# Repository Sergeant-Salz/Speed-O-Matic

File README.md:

# Speed'o'Matic

A small hardware/software project to build a velocity sensor for my [potato cannon](https://en.wikipedia.org/wiki/Potato_cannon).  
Using two strips of tinfoil stretched across a pipe, which are torn by the passing projectile, this system measures the travel time and calculates the velocity of the potato. Results are shown on a set of ultra-bright 7-segment displays.

## Overview

The goal of this project is to measure the velocity of a potato accelerated inside a PVC tube. The design uses a simple two-barrier timing system where the time difference between two breakpoints is used to estimate the projectile's average velocity.

To make the system detachable and reliable, a separate piece of pipe (matching the barrel diameter) is used. Two thin strips of aluminum foil are stretched across this pipe at fixed distances—these act as breakable electrical contacts. When the projectile passes through, it breaks the foils, triggering the timing logic.

The circuit is built around an ATMega microcontroller that measures and displays the travel time and optionally computes the velocity. The following sections describe the circuit and software in more detail.

## Hardware

The ATMega microcontroller handles all logic and is powered via a simple linear regulator. With the currently used LM1084 regulator, the input voltage can range from 5V to 29V.

In addition to measuring time, the microcontroller also drives four 7-segment displays to show timing and status information. To ensure maximum brightness (important for outdoor use), the displays are not multiplexed. Each display is driven by its own MOS4511 driver IC. Combined with 91Ω segment resistors, this setup results in an extremely bright, easily readable output - even in direct sunlight.

An extra push-button is included for to reset the software after a completed measurment.

The schematic above shows the complete circuit design.

Below is an image of the assembled PCB.  
The unpopulated capacitor footprints in the foreground were included for optional input debouncing, in case the mechanical barrier setup introduced signal glitches. In practice, these capacitors were not necessary, but the footprints remain available for future use.

Also note the empty space in the top-left corner, which was intended for a USB-A receptacle. See the [To-Do / Known Issues](#to-do--known-issues) section for more information.

## Software

The microcontroller is programmed via the Arduino platform and [MiniCore](https://github.com/MCUdude/MiniCore) board support package. The core logic is implemented as a state machine in `lichtschranke.ino`, with board-specific port definitions in separate header files.

### State Descriptions

- **`INIT`**
  - Entered on boot or when the reset button is pressed.
  - Displays the status of the two barriers (0/1) to indicate whether they are intact.
  - Transitions to `CAPTURE` once both barriers remain intact for 1 second.

- **`CAPTURE`**
  - Waits for the first foil to break (first interrupt).
  - Displays all zeros.
  - Transitions to `TRIGGERED_0` if the first barrier is broken.

- **`TRIGGERED_0`**
  - Waits for the second foil to break.
  - Displays the elapsed time since the first barrier was broken.
  - Transitions to `CAPTURE_DONE` once the second barrier is triggered.

- **`CAPTURE_DONE`**
  - Indicates successful capture; both barriers have been broken in the correct order.
  - Displays the time delta in milliseconds.
  - Returns to `INIT` when the reset button is pressed.

- **`GENERAL_ERROR`**
  - Currently unused; reserved for future error handling scenarios.

```mermaid
graph TD;
    INIT-->CAPTURE;
    CAPTURE-->TRIGGERED_0;
    TRIGGERED_0-->CAPTURE_DONE;
```

## Calibration

### Setup Description

For calibration, I used a Siglent SDG1032X function generator to produce precise reference timings on the circuit’s interrupt pins. Waveforms were verified using a Rigol DS1054Z oscilloscope and found to be accurate within a few nanoseconds.

### Measurements

In nanosecond mode, the system was found to be accurate to within ±2%. The shortest measurable delay is around 16 ns, though for intervals below 100 ns, accuracy decreases due to timer resolution limits.

## To-Do / Known Issues

### Interrupt Pins

The barrier sensors are currently routed to general-purpose pins, requiring the use of pin-change interrupts instead of dedicated external interrupts. While functional, this requires additional code to determine which pin triggered the interrupt and its edge direction. Future versions should re-route these signals to the ATMega's external interrupt pins for cleaner and more efficient interrupt service routines.

### USB-A Connector

The board currently includes a footprint for a USB-A connector, originally intended as an alternate power source. However, USB-A is poorly suited for this purpose. Consider replacing it with a USB micro-B or USB-C connector, or removing it altogether in future revisions.

### LED Brightness

The displays may actually be *too* bright for some conditions. In future revisions, consider using higher-value segment resistors to reduce brightness and power consumption, especially for indoor or low-light use.

### Timing Accuracy

To achieve higher precision—especially in the low nanosecond range—it may be worthwhile to forgo the Arduino framework and implement the timing-critical functions in bare-metal C. This would provide greater control over the microcontroller's behavior and open the door to low-level optimizations that improve accuracy and determinism.

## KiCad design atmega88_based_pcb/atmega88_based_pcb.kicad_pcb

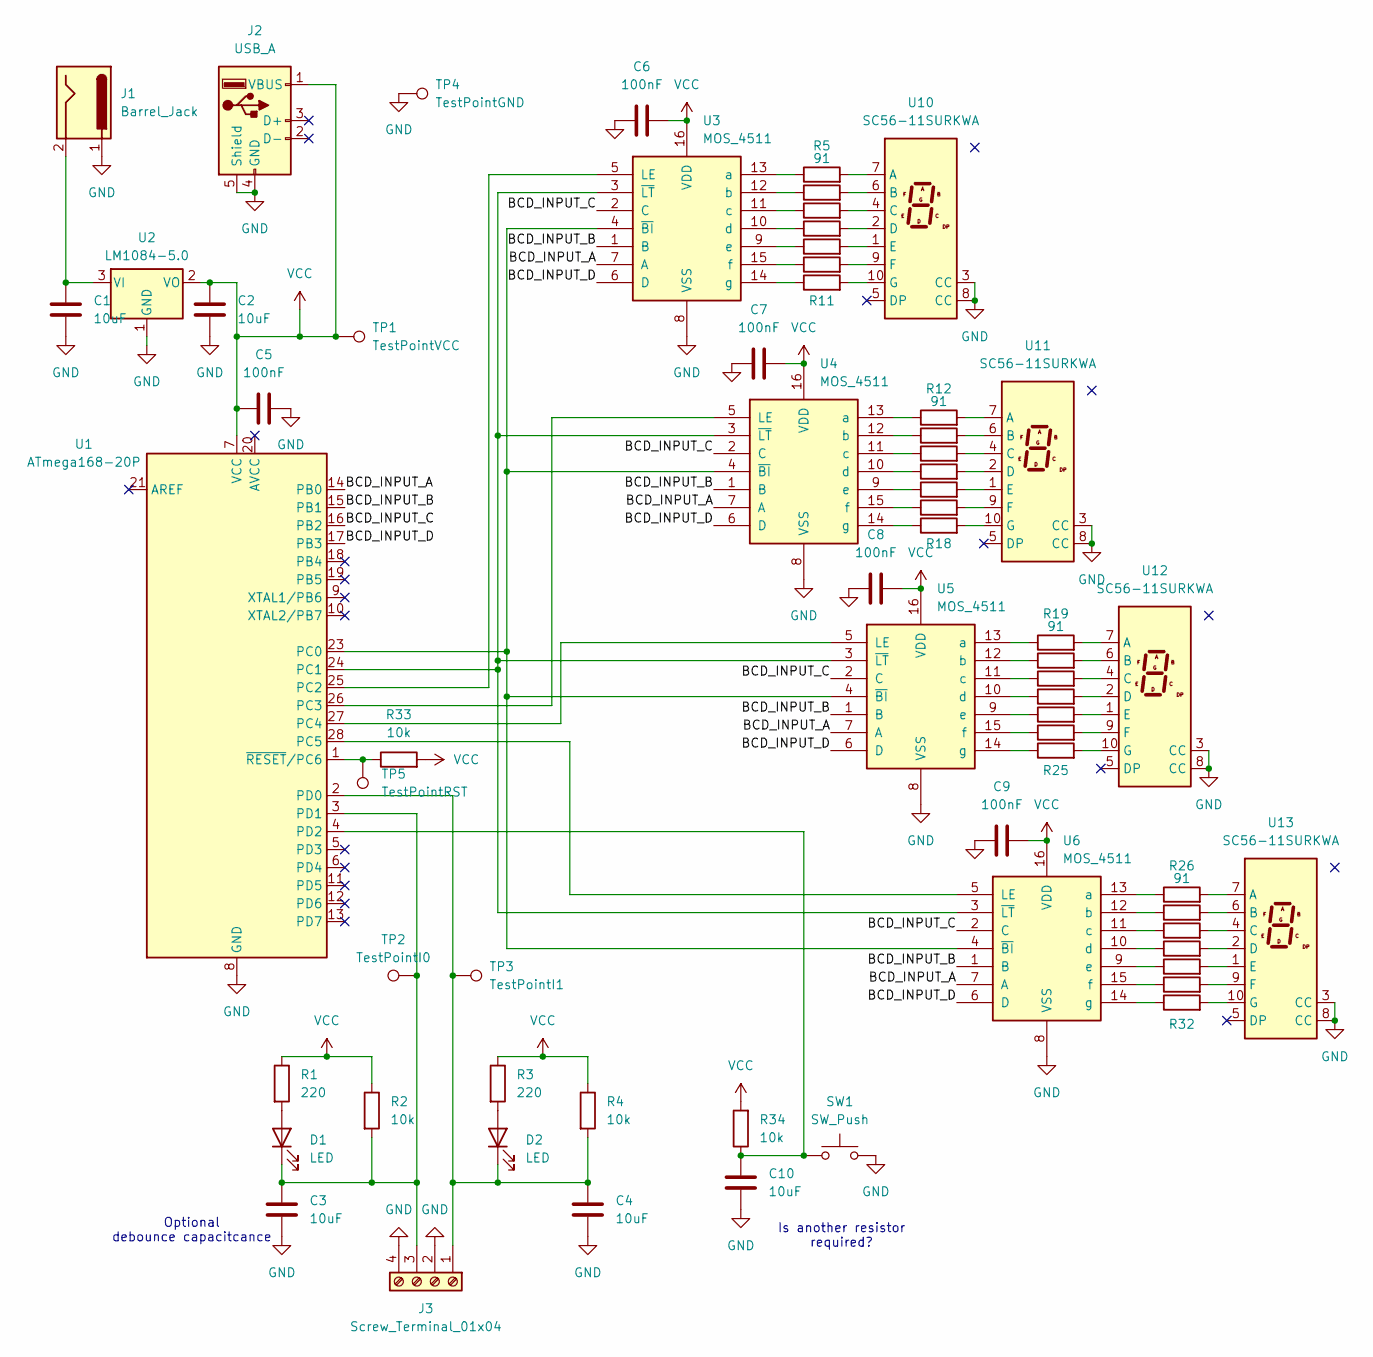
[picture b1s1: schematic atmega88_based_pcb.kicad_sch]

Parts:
C1, C2, C3, C4, C10: 10uF; CP_Radial_D10.0mm_P5.00mm
C5, C6, C7, C8, C9: 100nF; C_Axial_L3.8mm_D2.6mm_P7.50mm_Horizontal
D1, D2: LED; LED_D5.0mm
J1: Barrel_Jack; BarrelJack_CLIFF_FC68148S_SMT_Horizontal
J2: USB_A; USB_A_ASSMAN_AW
J3: Screw_Terminal_01x04; TerminalBlock_Phoenix_MPT-0,5-4-2.54_1x04_P2.54mm_Horizontal
R1, R3: 220; R_Axial_DIN0207_L6.3mm_D2.5mm_P7.62mm_Horizontal
R2, R4, R33, R34: 10k; R_Axial_DIN0207_L6.3mm_D2.5mm_P7.62mm_Horizontal
R5, R6, R7, R8, R9, R10, R11, R12, R13, R14, R15, R16, R17, R18, R19, R20, R21, R22, R23, R24, R25, R26, R27, R28, R29, R30, R31, R32: 91; R_Axial_DIN0207_L6.3mm_D2.5mm_P7.62mm_Horizontal
SW1: SW_Push; SW_SPST_Omron_B3F-40xx
TP1: TestPointVCC; TestPoint_Pad_1.0x1.0mm
TP2: TestPointI0; TestPoint_Pad_1.0x1.0mm
TP3: TestPointI1; TestPoint_Pad_1.0x1.0mm
TP4: TestPointGND; TestPoint_Pad_1.0x1.0mm
TP5: TestPointRST; TestPoint_Pad_1.0x1.0mm
U1: ATmega168-20P; DIP-28_W7.62mm
U2: LM1084-5.0; TO-220-3_Vertical
U3, U4, U5, U6: MOS_4511; DIP-16_W7.62mm
U10, U11, U12, U13: SC56-11SURKWA; D1X8K

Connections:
/BCD_INPUT_A: U1.14 (PB0), U3.7 (A), U4.7 (A), U5.7 (A), U6.7 (A)
/BCD_INPUT_B: U1.15 (PB1), U3.1 (B), U4.1 (B), U5.1 (B), U6.1 (B)
/BCD_INPUT_C: U1.16 (PB2), U3.2 (C), U4.2 (C), U5.2 (C), U6.2 (C)
/BCD_INPUT_D: U1.17 (PB3), U3.6 (D), U4.6 (D), U5.6 (D), U6.6 (D)
GND: C1.1, C2.1, C3.1, C4.1, C5.1, C6.2, C7.2, C8.2, C9.2, C10.1, J1.1, J2.4 (GND), J2.5 (Shield), J3.2, J3.4, SW1.2, TP4.1, U1.8 (GND), U1.22 (GND), U2.1 (GND), U3.8 (VSS), U4.8 (VSS), U5.8 (VSS), U6.8 (VSS), U10.3 (CC), U10.8 (CC), U11.3 (CC), U11.8 (CC), U12.3 (CC), U12.8 (CC), U13.3 (CC), U13.8 (CC)
unnamed: D1.2 (A), R1.2
unnamed: C3.2, D1.1 (K), J3.3, R2.2, TP2.1, U1.3 (PD1)
unnamed: D2.2 (A), R3.2
unnamed: C4.2, D2.1 (K), J3.1, R4.2, TP3.1, U1.2 (PD0)
unnamed: U1.23 (PC0), U3.4 (~BI), U4.4 (~BI), U5.4 (~BI), U6.4 (~BI)
unnamed: U1.24 (PC1), U3.3 (~LT), U4.3 (~LT), U5.3 (~LT), U6.3 (~LT)
unnamed: U1.25 (PC2), U3.5 (LE)
unnamed: U1.26 (PC3), U4.5 (LE)
unnamed: U1.27 (PC4), U5.5 (LE)
unnamed: U1.28 (PC5), U6.5 (LE)
unnamed: C10.2, R34.1, SW1.1, U1.4 (PD2)
unnamed: R33.1, TP5.1, U1.1 (~RESET/PC6)
unnamed: C1.2, J1.2, U2.3 (VI)
unnamed: R5.1, U3.13 (a)
unnamed: R6.1, U3.12 (b)
unnamed: R7.1, U3.11 (c)
unnamed: R8.1, U3.10 (d)
unnamed: R9.1, U3.9 (e)
unnamed: R10.1, U3.15 (f)
unnamed: R11.1, U3.14 (g)
unnamed: R12.1, U4.13 (a)
unnamed: R13.1, U4.12 (b)
unnamed: R14.1, U4.11 (c)
unnamed: R15.1, U4.10 (d)
unnamed: R16.1, U4.9 (e)
unnamed: R17.1, U4.15 (f)
unnamed: R18.1, U4.14 (g)
unnamed: R19.1, U5.13 (a)
unnamed: R20.1, U5.12 (b)
unnamed: R21.1, U5.11 (c)
unnamed: R22.1, U5.10 (d)
unnamed: R23.1, U5.9 (e)
unnamed: R24.1, U5.15 (f)
unnamed: R25.1, U5.14 (g)
unnamed: R26.1, U6.13 (a)
unnamed: R27.1, U6.12 (b)
unnamed: R28.1, U6.11 (c)
unnamed: R29.1, U6.10 (d)
unnamed: R30.1, U6.9 (e)
unnamed: R31.1, U6.15 (f)
unnamed: R32.1, U6.14 (g)
unnamed: R5.2, U10.7 (A)
unnamed: R6.2, U10.6 (B)
unnamed: R7.2, U10.4 (C)
unnamed: R8.2, U10.2 (D)
unnamed: R9.2, U10.1 (E)
unnamed: R10.2, U10.9 (F)
unnamed: R11.2, U10.10 (G)
unnamed: R12.2, U11.7 (A)
unnamed: R13.2, U11.6 (B)
unnamed: R14.2, U11.4 (C)
unnamed: R15.2, U11.2 (D)
unnamed: R16.2, U11.1 (E)
unnamed: R17.2, U11.9 (F)
unnamed: R18.2, U11.10 (G)
unnamed: R19.2, U12.7 (A)
unnamed: R20.2, U12.6 (B)
unnamed: R21.2, U12.4 (C)
unnamed: R22.2, U12.2 (D)
unnamed: R23.2, U12.1 (E)
unnamed: R24.2, U12.9 (F)
unnamed: R25.2, U12.10 (G)
unnamed: R26.2, U13.7 (A)
unnamed: R27.2, U13.6 (B)
unnamed: R28.2, U13.4 (C)
unnamed: R29.2, U13.2 (D)
unnamed: R30.2, U13.1 (E)
unnamed: R31.2, U13.9 (F)
unnamed: R32.2, U13.10 (G)
VCC: C2.2, C5.2, C6.1, C7.1, C8.1, C9.1, J2.1 (VBUS), R1.1, R2.1, R3.1, R4.1, R33.2, R34.2, TP1.1, U1.7 (VCC), U2.2 (VO), U3.16 (VDD), U4.16 (VDD), U5.16 (VDD), U6.16 (VDD)

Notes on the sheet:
Optional debounce capacitcance
Is another resistor required?

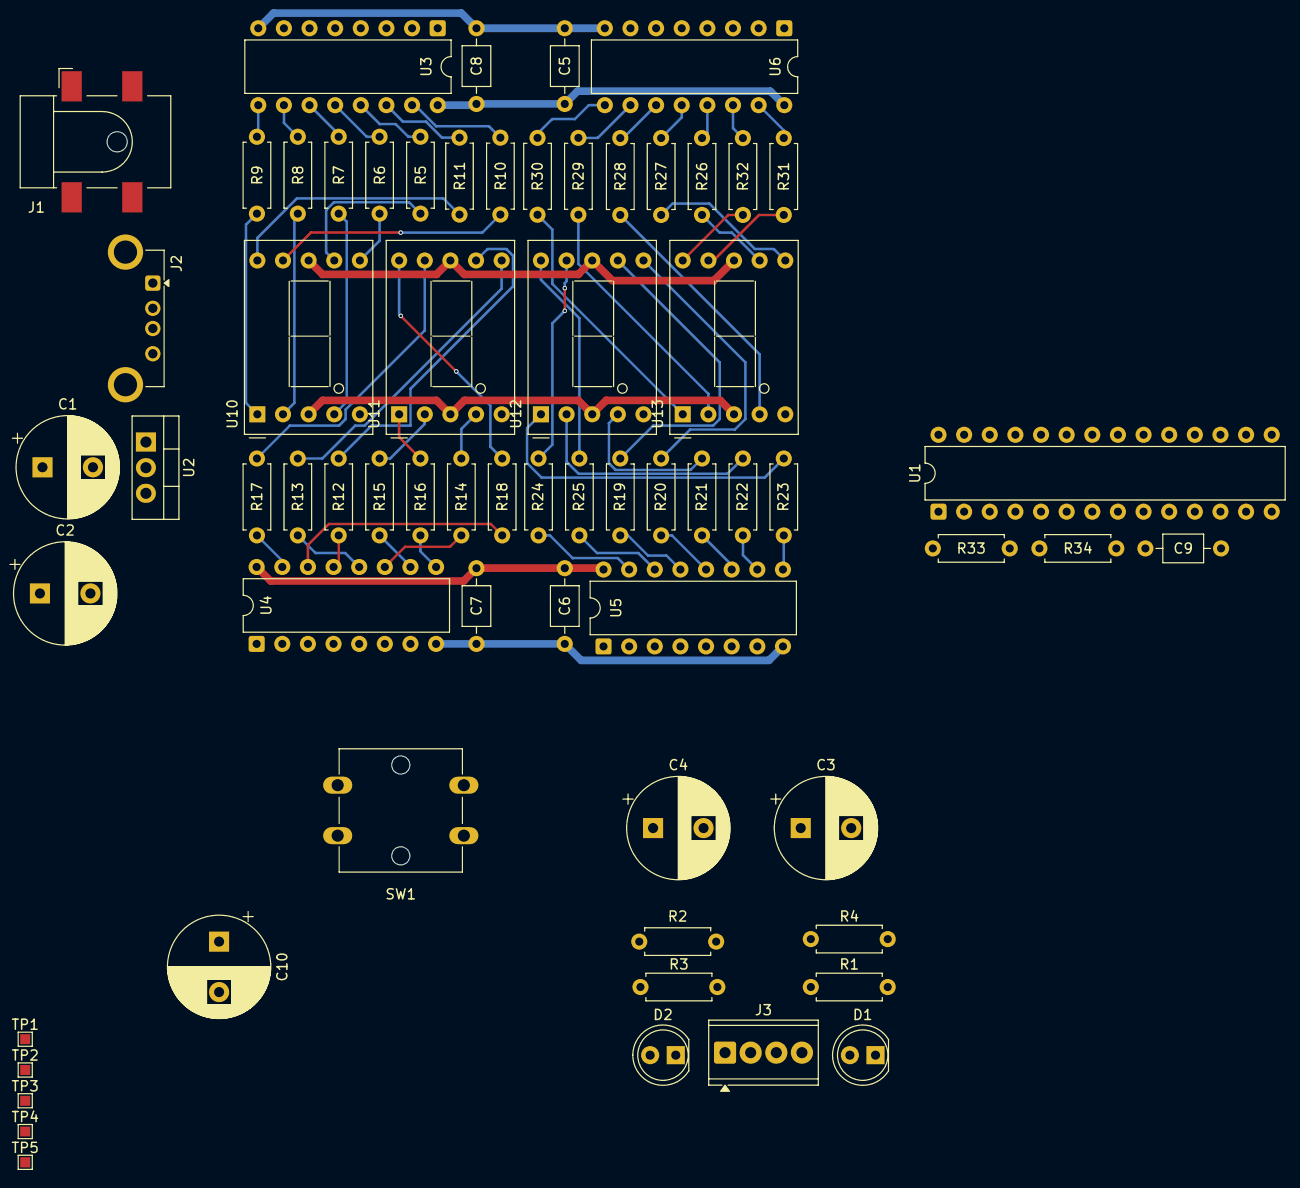
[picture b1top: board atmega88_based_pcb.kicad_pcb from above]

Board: 2 copper layers, 65 parts (0 on the bottom side), 75 nets.

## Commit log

2025-03-23 Initial arduino src code commit
2025-03-23 Fixed INIT transition, interrupt pins and logging improvement
2025-03-24 Fix latching for display drivers Fix time delta computation
2025-03-24 Initial commit of KiCad files
2025-04-15 Small fixes to comments and debug macro
2025-04-15 Added ATmega168 board pin definitions
2025-04-15 Tied AVCC to VCC and changed interrupt pins to use PD3/4 for external interrupts instead of PCINT
2025-04-23 Added README
2025-04-23 Fix mermaid diagram
2025-04-23 PCINT first draft
2025-04-24 Added some page metadata to schematic
2025-04-24 Added schematic to README
2025-04-24 Changed title
2025-04-24 Renamed src code directory^
2025-04-24 Added more general attach/detachInterrupt overwrites
2025-04-24 Added reset button support
2025-04-24 Fixed number display order
2025-04-24 Changed interrupt order to match user intuition
2025-04-24 Improved overview section, added LED brightness issue
2025-04-27 Added photograph of finished PCB to README
2025-05-12 Removed interrupt ordering constraint Added microsecond display mode
2025-05-12 Fixed flash interval in microsecond mode
2025-05-12 Added microsecond mode to README.md
2025-06-07 Added section on timing calibration
